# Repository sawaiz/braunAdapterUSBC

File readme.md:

# Braun USB-C Power Adapter
A charger adapter to provide a USB-C interface to some of the following products

- Braun
- Oral-B

Or any other simple 12V charger that consumes less than 500mA. Check your charger or device manual for compatiblity. Generally, these are shavers, epilators, electric toothbrushes and similar products. This provides a small convinent charger that can be convinently be stored in along with the toothbrush in its own travel case. Also, it lets you only bring a single charger and cable with you on your travels for all your electronics, letting you pack lighter.

![travelCase]

This twitter [thread](https://twitter.com/SawaizSyed/status/1172068551148146688) can provide background and further updates.

**This is still in Alpha and has not been tested. Please wait for 1V0 Relese candidate or continue at your own peril**

**One was assembled and works with non PD chargers, I think I have quite a few bad solder joints on the USB-C connector, I'll be testing again with a cleaner paste application with a stencil. Upgraded to Beta.**

## Design
The stock charger provided with my Oral-B Genius 9000 travel case is rated at 12V and 400mA. The design will be set to match the voltage and exceed the current requirements, so it works with as many similar porducts as possible. 

![renderIso1]

Using the USB 5V avalibilty as more adapter suppourt rather than the 15V and boosting the voltage to 12V from the 5V@3A would provide 800mA with perfect efficency letting us rate our charger safely at 500mA. The 12V profile is also being completely avoided since the 12V profile only existed in the REV 1.0 of the power delivery protocol and is not compatible with current standards. Using the 5V profile also allows us to not need a negotiator and instead just use two passive 5.1K resistors on the CC lines.

![renderIso2]

### Boost Converter
The Microchip [MIC2290](http://ww1.microchip.com/downloads/en/DeviceDoc/MIC2290-075A-Switch-PWM-Boost-Regulator-with-Internal-Schottky-Diode-and-Undervoltage-Lockout-DS20006038A.pdf) is a easy to implement boost converter with a intergrated switch and didoe requiring only external passives. A 10uH inductor, some input and output capacitors and resistors to set the output voltage are all that are needed. The 43.2K and 5k resistors are from the example in the datasheet to set the voltage to 12V.

![schematic]

## BOM
The bill of materials is availible in [`bom.csv`](bom.csv) and is copied into a table below.

| Ref Des | Qty | Manufacturer | MPN              | Description                       |
| ------  | --- | ------------ | ---------------- | --------------------------------- |
| C1 C2   | 2   | Samsung      | CL21A106KOQNNNG  | CAP CER 10UF 16V X5R 0805         |
| J1      | 1   | Amphenol ICC | 12401610E4#2A    | CONN RCP USB3.1 TYPEC 24P SMD RA  |
| L1      | 1   | Taiyo Yuden  | NRS5030T100MMGJ  | FIXED IND 10UH 1.7A 70 MOHM SMD   |
| R1 R2   | 2   | Yageo        | RC0402JR-075K1L  | RES SMD 5.1K OHM 5% 1/16W 0402    |
| R3      | 1   | Yageo        | RC0402FR-0743K2L | RES SMD 43.2K OHM 1% 1/16W 0402   |
| R4      | 1   | Yageo        | RC0402FR-074K99L | RES SMD 4.99K OHM 1% 1/16W 0402   |
| U1      | 1   | Microchip    | MIC2290YML-TR    | IC REG BOOST ADJ 750MA 8MLF       |

A [Octopart](https://octopart.com/bom-tool/Fi5WwdJ5) BOM is also availible to simplify ordering. 

## Assembly
Assembly is all surface mount with componets on one side of the board to make PNP assembly easy.

![assembly]

Solder paste can be applied with 26ga+ syringe, or with a stencil of the top paste layer, and then reflowed. The componets can then be placed, taking note of the two that are polarity dependent being U1 and J1 as marked in the assembly layer.

![soldered]

Then a connector from a charger can be removed and after checking polarity, soldered on to the two though hole pads denoting *12V* and *GND*.

![connector]

## Ordering
I havent tested the exported gerbers fully, I just upload the KiCad file. The board will be a standard 1.6mm (0.063") two-layer FR4 with 6/6mil spacing, plated though vias. These are generally the defaults boards so they can be made by most fabrication houses.

*PCB Dimensions*
|        | Width | Height |
| ------ | ----- | ------ |
| Inches | 0.48  |  0.75  |
| mm     | 12.1  |  19.1  |

At OSH Park 3 boards will cost 1.75 USD. This includes shipping internationally. Components not including the Braun connector come to 3.46 USD at Digikey. These are all in low quantity.

![renderTop]

[renderTop]:  /img/renderTop.png   "Render with view from above"
[renderIso1]: /img/renderIso1.png  "Isoemtric render from connector"
[renderIso2]: /img/renderIso2.png  "Isometric render from outputs"
[assembly]:   /img/assembly.png    "Assembly drawing for component positon"
[schematic]:  /img/schematic.png   "Schematic of the circuit"
[soldered]:   /img/soldered.jpg    "A assembled and soldered board"
[connector]:  /img/connector.jpg   "The proprietary connector soldered to the board"
[travelCase]: /img/travelCase.jpg  "Full device stored in travel case"

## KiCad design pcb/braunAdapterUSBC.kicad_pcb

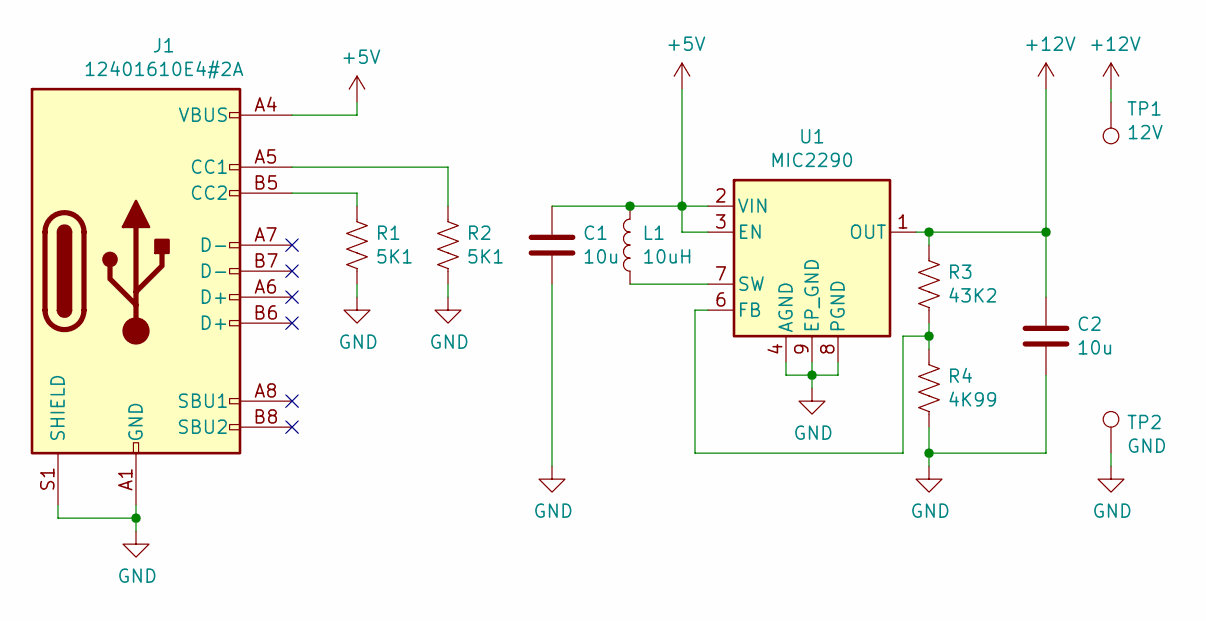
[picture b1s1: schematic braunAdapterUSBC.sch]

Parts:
C1, C2: 10u; C_0805_2012Metric
J1: 12401610E4#2A; USB_C_Receptacle_Amphenol_12401610E4-2A
L1: 10uH; L_Taiyo-Yuden_NR-50xx
R1, R2: 5K1; R_0402_1005Metric
R3: 43K2; R_0402_1005Metric
R4: 4K99; R_0402_1005Metric
TP1: 12V; TestPoint_THTPad_D2.0mm_Drill1.0mm
TP2: GND; TestPoint_THTPad_D2.0mm_Drill1.0mm
U1: MIC2290; Micrel_MLF-8-1EP_2x2mm_P0.5mm_EP0.8x1.3mm_ThermalVias

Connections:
+5V: C1.1, J1.A4 (VBUS), J1.A9 (VBUS), J1.B4 (VBUS), J1.B9 (VBUS), L1.2, U1.2 (VIN), U1.3 (EN)
+12V: C2.1, R3.1, TP1.1, U1.1 (OUT)
GND: C1.2, C2.2, J1.A1 (GND), J1.A12 (GND), J1.B1 (GND), J1.B12 (GND), J1.S1 (SHIELD), R1.2, R2.2, R4.2, TP2.1, U1.4 (AGND), U1.8 (PGND), U1.9 (EP_GND)
unnamed: J1.A5 (CC1), R2.1
unnamed: J1.B5 (CC2), R1.1
unnamed: L1.1, U1.7 (SW)
unnamed: R3.2, R4.1, U1.6 (FB)

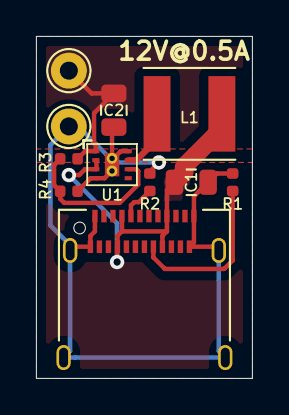
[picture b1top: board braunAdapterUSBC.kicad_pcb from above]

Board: 2 copper layers, 12.0 x 19.0 mm, 11 parts (0 on the bottom side), 7 nets.

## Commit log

2019-09-12 Added renders to readme and gerbers
2019-09-12 Added octopart link
2020-03-16 Updated readme, added pictures, Upgraded to BETA status.
